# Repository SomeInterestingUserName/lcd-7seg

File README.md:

# lcd-7seg
A 4-digit 7-segment display module based on the NXP PCF8562 driver IC. The PCB fits a Lumex LCD-S401C52TR display. With the exception of Backplanes 2-4, all other pins of the PCF8562 are broken out to headers or jumpers to allow for evaluation of advanced features.

**Note:** The NXP datasheet currently lists the PCF8562 as "Not Recommended for New Designs". The PCF85162 (note the additional "1") is a drop-in replacement for this part. However, the PCF8562 (without the "1") is still widely available, and in fact appears to be available in larger quantities at the moment (as of January 2021).

## Hardware Notes
* The PCB was designed to fit JLCPCB's design rules. Although a quick cross-check shows these rules are compatible with some other PCB fabs, please check that they meet your preferred PCB fab's specs.
* If PCBs are manufactured using the HASL (Hot-Air Solder Leveling) surface finish, small solder bumps may be left on the TSSOP footprint's pins. It is recommended to clean these with some solder wick to make IC alignment easier. This is only necessary for the PCF8562 (U1).
* This board can be hand-soldered, although some practice is recommended. All passives are 0805 size, and the PCF8562 can be quickly "drag-soldered" using plenty of flux. Be sure to closely inspect the PCF8562 pins for solder bridges and touch-up with solder wick as necessary.
* All 3-way jumpers must have **one** option selected for the module to function correctly. The default values are:
    * `A0`: `0`
    * `A1`: `0`
    * `A2`: `0`
    * `I2C ADDR`: `0x70`
    * `OSC`: `INT`
    * `VLCD`: `VDD`

## Datasheets (from mouser.com)
* [PCF8562](https://www.mouser.com/datasheet/2/302/PCF8562-1127585.pdf) (Driver IC)
* [LCD-S401C52TR](https://www.mouser.com/datasheet/2/244/LCD-S401C52TR-1141159.pdf) (LCD)

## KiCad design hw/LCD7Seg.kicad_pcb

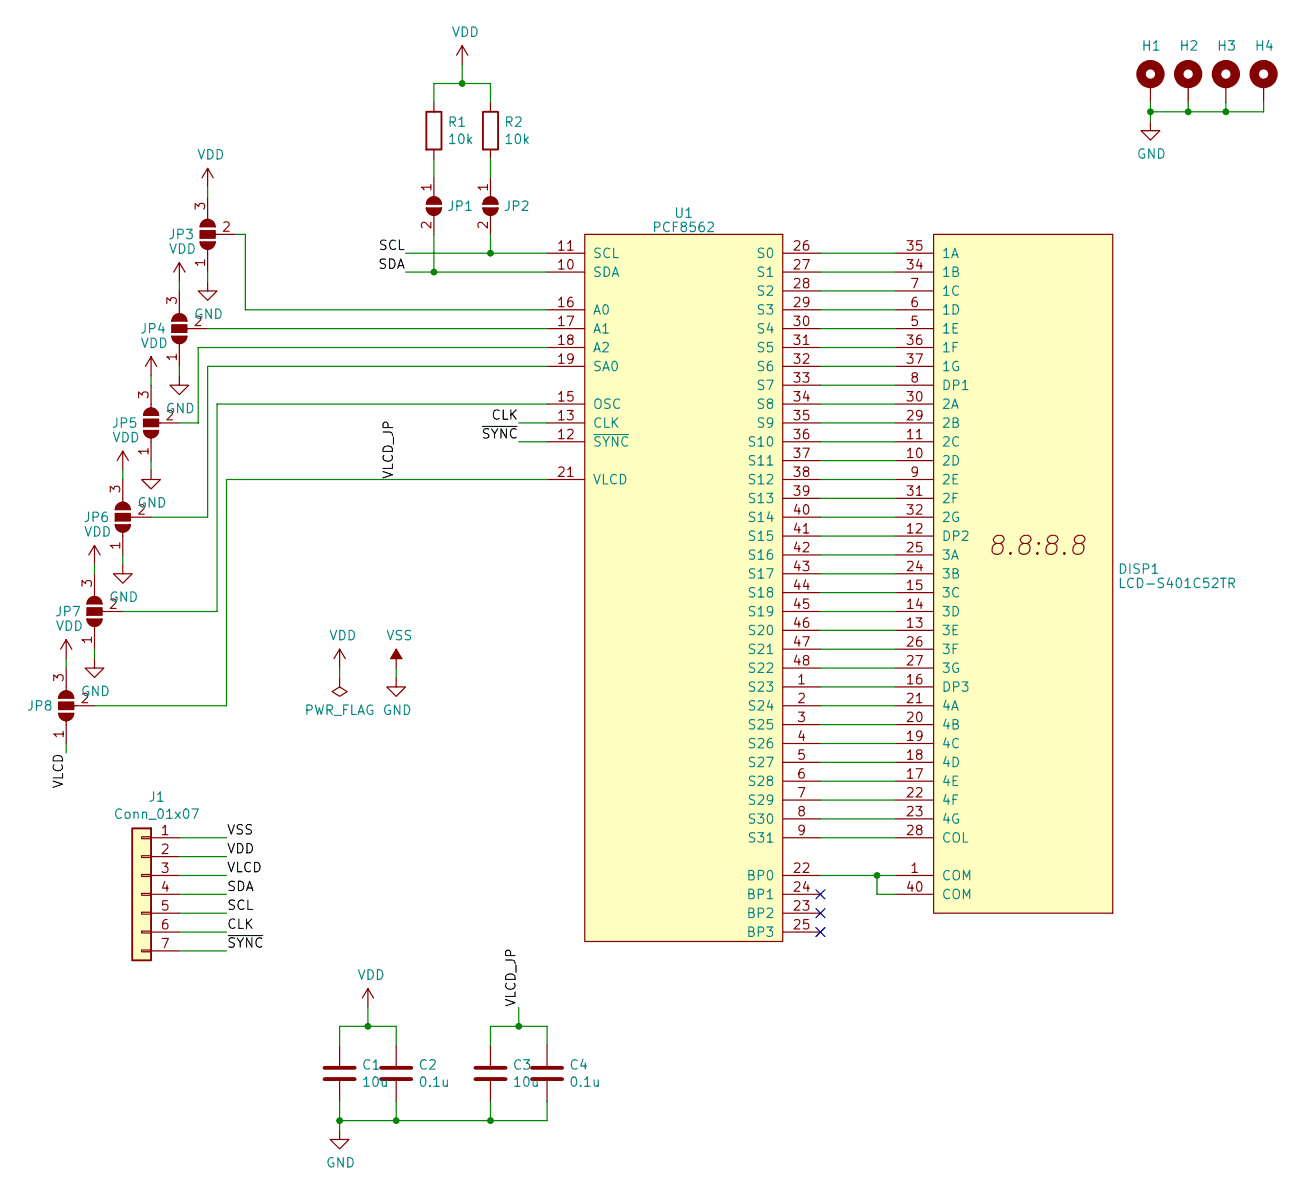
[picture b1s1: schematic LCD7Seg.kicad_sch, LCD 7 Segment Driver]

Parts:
C1, C3: 10u; C_0805_2012Metric
C2, C4: 0.1u; C_0805_2012Metric
DISP1: LCD-S401C52TR; S401C52TR
H1, H2, H3, H4: MountingHole_Pad; MountingHole_3.2mm_M3_Pad_Via
J1: Conn_01x07; PinHeader_1x07_P2.54mm_Vertical
JP1, JP2: SolderJumper_2_Open; SolderJumper-2_P1.3mm_Open_TrianglePad1.0x1.5mm
JP3, JP4, JP5, JP6, JP7, JP8: SolderJumper_3_Open; SolderJumper-3_P2.0mm_Open_TrianglePad1.0x1.5mm
R1, R2: 10k; R_0805_2012Metric
U1: PCF8562; TSSOP-48_6.1x12.5mm_P0.5mm

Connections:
/CLK: J1.6, U1.13 (CLK)
/SCL: J1.5, JP2.2 (B), U1.11 (SCL)
/SDA: J1.4, JP1.2 (B), U1.10 (SDA)
/VLCD: J1.3, JP8.1 (A)
/VLCD_JP: C3.1, C4.1, JP8.2 (C), U1.21 (VLCD)
/~SYNC: J1.7, U1.12 (~SYNC)
GND: C1.2, C2.2, C3.2, C4.2, H1.1, H2.1, H3.1, H4.1, J1.1, JP3.1 (A), JP4.1 (A), JP5.1 (A), JP6.1 (A), JP7.1 (A), U1.20 (VSS)
unnamed: DISP1.1 (COM), DISP1.40 (COM), U1.22 (BP0)
unnamed: DISP1.5 (1E), U1.30 (S4)
unnamed: DISP1.6 (1D), U1.29 (S3)
unnamed: DISP1.7 (1C), U1.28 (S2)
unnamed: DISP1.8 (DP1), U1.33 (S7)
unnamed: DISP1.9 (2E), U1.38 (S12)
unnamed: DISP1.10 (2D), U1.37 (S11)
unnamed: DISP1.11 (2C), U1.36 (S10)
unnamed: DISP1.12 (DP2), U1.41 (S15)
unnamed: DISP1.13 (3E), U1.46 (S20)
unnamed: DISP1.14 (3D), U1.45 (S19)
unnamed: DISP1.15 (3C), U1.44 (S18)
unnamed: DISP1.16 (DP3), U1.1 (S23)
unnamed: DISP1.17 (4E), U1.6 (S28)
unnamed: DISP1.18 (4D), U1.5 (S27)
unnamed: DISP1.19 (4C), U1.4 (S26)
unnamed: DISP1.20 (4B), U1.3 (S25)
unnamed: DISP1.21 (4A), U1.2 (S24)
unnamed: DISP1.22 (4F), U1.7 (S29)
unnamed: DISP1.23 (4G), U1.8 (S30)
unnamed: DISP1.24 (3B), U1.43 (S17)
unnamed: DISP1.25 (3A), U1.42 (S16)
unnamed: DISP1.26 (3F), U1.47 (S21)
unnamed: DISP1.27 (3G), U1.48 (S22)
unnamed: DISP1.28 (COL), U1.9 (S31)
unnamed: DISP1.29 (2B), U1.35 (S9)
unnamed: DISP1.30 (2A), U1.34 (S8)
unnamed: DISP1.31 (2F), U1.39 (S13)
unnamed: DISP1.32 (2G), U1.40 (S14)
unnamed: DISP1.34 (1B), U1.27 (S1)
unnamed: DISP1.35 (1A), U1.26 (S0)
unnamed: DISP1.36 (1F), U1.31 (S5)
unnamed: DISP1.37 (1G), U1.32 (S6)
unnamed: JP1.1 (A), R1.2
unnamed: JP2.1 (A), R2.2
unnamed: JP3.2 (C), U1.16 (A0)
unnamed: JP4.2 (C), U1.17 (A1)
unnamed: JP5.2 (C), U1.18 (A2)
unnamed: JP6.2 (C), U1.19 (SA0)
unnamed: JP7.2 (C), U1.15 (OSC)
VDD: C1.1, C2.1, J1.2, JP3.3 (B), JP4.3 (B), JP5.3 (B), JP6.3 (B), JP7.3 (B), JP8.3 (B), R1.1, R2.1, U1.14 (VDD)

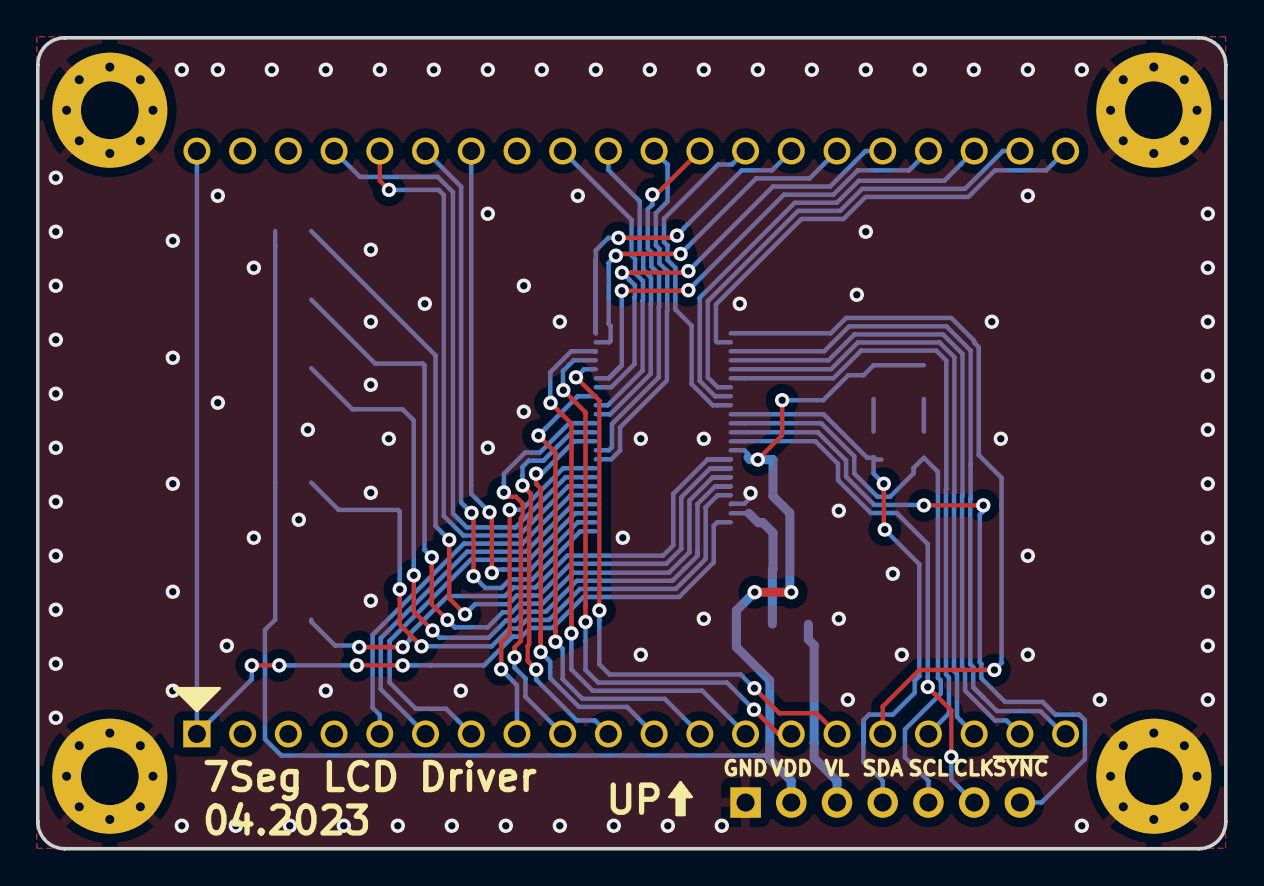
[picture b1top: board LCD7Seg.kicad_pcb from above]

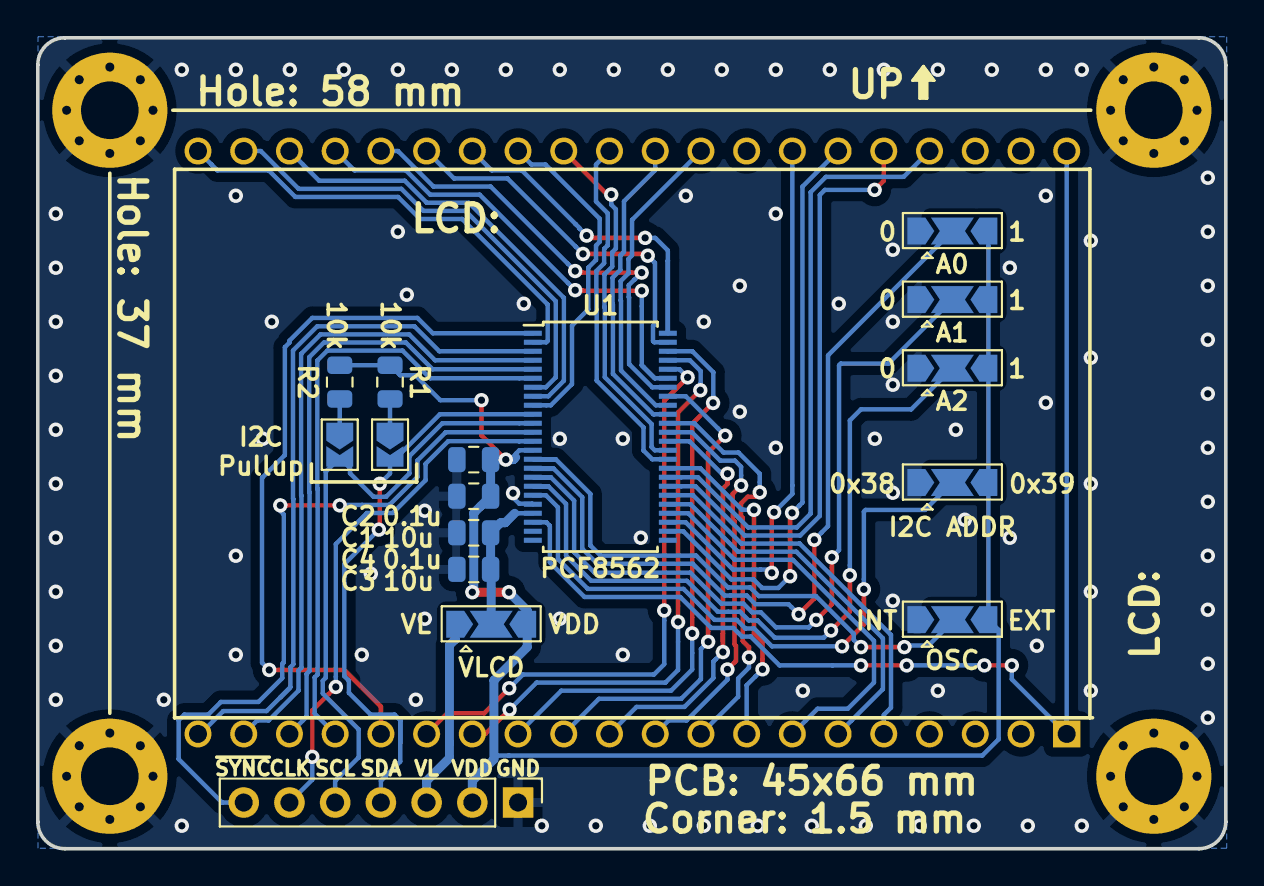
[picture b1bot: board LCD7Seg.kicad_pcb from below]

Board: 2 copper layers, 66.0 x 45.1 mm, 21 parts (16 on the bottom side), 48 nets.

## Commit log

2021-01-24 Add Hardware Files
2021-01-24 Add datasheet links
2021-01-24 Add default jumper values
2021-02-02 Add info to schematic and pcb files
2021-02-02 Change i2c address on pcb silkscreen--should be 0x38 and 0x39
2023-04-18 Add .gitignore to ignore `.DS_Store` files
2023-04-18 Migrate to KiCad 7.0
    Old files can be found at `legacy/`
    KiCad's PCB editor does fills a bit differently now, changing the copper
    fill pattern on the board. This warranted a new revision code on the
    PCB.
2023-04-18 Add PDFs of schematic and PCB
2023-04-29 Add C code
2023-04-29 Add images
2023-10-26 microseconds not nanoseconds
